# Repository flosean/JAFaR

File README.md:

# Fork from JAFaR (Just Another Fatshark Receiver Module)

__DIY OpenSource 48ch receiver OSD integrated__

The aim of the project is to build an opensource 48ch receiver for Fatshark goggles which has to be easy to develop,
upgrade and maintain. And, of course, it must be cheap!

* 48ch (8 channels for 6 bands, including race band and low race band)
* No external switch, or hall effect sensor, or buzzer, it must use __only__ the goggles buttons (up-down)
* Auto search feature
* It should include the “scanner” feature (see recent project here https://github.com/MikyM0use/OLED-scanner)
* Frequency selection via OSD inside the goggles
* I tested it only with Fatshark HD but the module should work with every Fatshark with the RX external module (like Dominator V1, V2, V3, HD, HD2...)

This project uses the “RX5808” receiver module, which can be hacked to be SPI-programmed by a microcontroller (more details later).
So what I needed is a micro controller with an easy and well-know software IDE… nothing better than Arduino. So I decided to use an Atmega 328p as micro controller.

To select the frequency there's a series of menus on the screen inside the goggles, the
useful TVOUT Arduino library is perfect and requires just a couple of resistors
(http://playground.arduino.cc/Main/TVout).
A digital switch (TS5A3359) allow to switch from OSD to the normal receiving video from the quadcopter.

The project is mainly divided into two PCBs:
* one main base module
* one "diversity" daughterboard (optional)

it's also possible to use an SPI-OLED display and use the module as standalone RX.

##Table of contents
* [Main module](#main-module)
	* [DIY Instructions](#diy-instructions)
	* [MAIN MODULE Troubleshooting](#main-module-troubleshooting)
* [Diversity module](#diversity-module)
* [OLED module](#oled-module)
* [STANDALONE mode](#standalone-mode)
* [Reference thread](#reference-thread)
* [FAQ:](#faq)
* [Donations:](#donations)

##Main module

This is the main RX module, usable alone as a receiver module, but if you connect an
"external" module, the onboard microcontroller can decide which RX module has better
reception (so-called "diversity") based on the received signal strength. Indeed, this
RX5808 modules has an analog output called RSSI proportional on the "quality" of the
received video signal. The receiving video channel (frequency) is set by the user using an OSD menu.

__MAIN MODULE (V4.1) BOM__

https://docs.google.com/spreadsheets/d/1CrZzOQHyK_d1VfHCQKwdNuoyMji0IYryI1VuffojdGA/edit?usp=sharing

__LEGACY MAIN MODULE (V3.2)__

This module is actually the same as the v4, but it doesn't have the buffer on the RSSI output,
and the PCB allows the use of a capacitor OR a resistor on the video out. DON'T use both! after some
tests I realized that a 10ohm resistor (and no cap) is enough.

(the back side is the same of the v4.0).

__LEGACY MAIN MODULE (V3.2) BOM__

https://docs.google.com/spreadsheets/d/1-763imBV3QsQ71GKDZH-BirTz1k32szNuJZUKQrE00g/edit?usp=sharing

###DIY Instructions

1. Remove the shield of the RX5808 module and desolder the resistor marked by the arrow. This
is the SPI-mod required to control the module with an external microcontroller.

2. Follow the instructions on the page https://www.arduino.cc/en/Tutorial/ArduinoISP to burn the bootloader (select __"Arduino Pro Mini 5v 16MHz"__ as target board)
using the pins in the upper right corner of the board

3. Use the FTDI connections in the left side of the board to upload the code present in the
Github page of the project. Please remember to copy all the subfolders of "libs" dir in the
libraries folder of Arduino (e.g. /Arduino/libraries).
Here you can find more infos and alternative methods to import the libraries:
https://www.arduino.cc/en/Guide/Libraries

4. When you power on the module, BOTH the leds (upper left corner of the pcb) must be on, and you must see a relatively stable splash screen for about 5 seconds

5. The very first time you power on the module, it need to calibrate itself. So please turn on the module with a working Vtx a couple of meter away (the video frequency doesn't matter). This process can take a while (about 30-50 seconds).

6. You can now use the "selection" buttons on the goggles to scroll up/down the menu to select the band

7. After the timeout of the countdown (upper left corner of the screen) you entered the frequency selection (of the selected band)

8. Scroll up/down to select the frequency and wait the timeout

9. At this moment only one led on the module has to be ON, it means that the RX video output is routed to the video_input of the goggles. If you have a Vtx near, you should see the video coming from it.

10. If you press the "selection" buttons of the goggles now, you change the frequency by the 8 frequencies of the previously selected band.

###MAIN MODULE Troubleshooting

After the initial calibration, the module must turn on in couple of seconds and you must see the splash screen for some seconds before the "band selection" screen.
In the "band selection" screen you can see the 5 bands with the percentage of the maximum RSSI detected on that band. At least one of the band must be at 98-100%.
If you "enter" one band, every channel must shows a different percentage of RSSI, otherwise the SPI-mod of the module could be failed.

__Unable to flash/Aduino issues:__

(thanks to pHysiX for the help in this section!)
Got the error "no reply" when trying to load the firmware:
the ATmega microcontroller is not soldered properly / there is a short on some pins.
try a quick solder, clean and reflow.

Got the error "incorrect signature" when trying to load the firmware:
This means Arduino is able to pick up the ATMega, but it was not communicating as expected.
This is related to poor soldering of the crystal. It's possible to do the crystal using
an iron, but I strongly recommend using flow method/hot air to do this, to make sure you
don't short the three legs accidentally onto the metal case.

__Display issues:__

They are mostly related to poor soldering for the OSD components on the board. Go back and
reflow especially the Switch, and then just make sure to clean up and touch up all the caps
and resistors near and around the switch.

If you have an external monitor, you can bypass the digital switch by power on the module with external 5v and connecting the "video in" of the monitor on the test point marked in yellow the picture:

and you should see the splash screen and the menu.

If you connect the "video in" of the monitor to the test point marked in green, you should see the initial scanning (used to determine the % of the RSSI on each channel), this means a sequence of different "fogs" and (at least) one "good" image (for a fraction of second), if you have a Vtx + cam transmitting.

__Frequency issues:__

If the module is having trouble Setting Frequency, or you are not getting video when you are
on the right channel and frequency, make sure the SPI mod has been done, and that the RX5808
is soldered on well. Pretty hard to mess this part up.

##Diversity module

The diversity module is an optional second receiver, connected to the "main" base module, it has:
* integrated linear 5v regulator with ENABLE feature connected to the VCC of the main module.
In fact power a second module from the internal goggles voltage regulator IS VERY DANGEROUS!
* an optional operational buffer for RSSI signal (I noticed that lately modules seems to be more delicate)

Please notice that because of the linear regulator on the module, it's not possible to use a 3s battery to power the diversity module.

You have two options to connect the diversity module to the base module:
* by pins: putting diversity module on top of the base one
* by jst connector: following the schematic in the image below. I used a 8-pin JST because it's used also on some FC and it's more simple to find, even if only 7 pins are used.

__DIVERSITY MODULE (V2.1) BOM__

https://docs.google.com/spreadsheets/d/1OpagubuxicmGTKqOHWwWdxZxY6wCs_DZqTYRxVoD4Tc/edit?usp=sharing

##OLED module
It's possible to use an external SPI OLED module in case of any problems with the internal OSD
or to use the module with an external monitor / different goggles.

It's important that the module has only SDA/SCL/RES/DC pins.

To use the OLED module instead of the internal OSD, uncomment  the line:

```
#define USE_OLED
```

in the file const.h

please remember to comment #define USE_DIVERSITY!

__Connections__

| ATMEGA328p pin        |  PCB silkscreen name           | OLED silkscreen name  |
| :-------------------:	|:------------------------------:| :--------------------:|
| VCC      				| 		EN 						| 		VCC 			|
| GND      				| GND 							| 					GND |
| 8      				| SSEL 							| 				SCL 	|
| A1      				| RSSI      					|   		SDA 		|
| A4 					|  NOT CONNECTED      			|    	NOT CONNECTED 	|
| 11 					| SDA      						|    DC 				|
| 13				 	| CLK      						|    RESET 				|

...or graphically:

there's also a "PCB" inside the PCBs folder, but it's just a simple adapter.

##Standalone mode

It's possible to use the project also as a standalone receiver to be used in combination
with any external monitor or other kind of goggles.

In this case you must uncomment the line

```
#define STANDALONE
```

in the file const.h. You can use the standalone mode either with OSD or with the external OLED module.

to change band/channel, the connections are the following (every normally-open momentary switch will do the job):

_UPDATE:_

it's now possible to use a "standalone module" to use the usually OSD menu on every monitor/goggles, look into /pcb/standalone_module

features:
a 5v BIG voltage regulator (up to 3/4s)
3.5mm jack output compatible with Fatshark pinout
up/down/enter joystick (work in progress to get the "back to the main menu" function by lon press the central button)
external battery /diversity module connection

__STANDALONE MODULE (V2.0) BOM__
https://docs.google.com/spreadsheets/d/1Lyl0Xg57OcXvrLwUwM6oeHDwdGa9hMxbpv7bcDlpDU4/edit?usp=sharing

##Reference thread

http://www.rcgroups.com/forums/showthread.php?t=2619124 while I'm still writing the readme :)

##FAQ

why the OSD is on the blank screen?
it’s simpler because one cannot have to recognize the vsync and the hsync pulses.

why the switch is so small and hard to solder?!?
I need a small 3-way switch, if you have a "simpler" one, just tell me :)

please note that you try and use this project AT YOUR OWN RISK!

##Donations

Hardware or paypal donations to carry on the project are always accepted.

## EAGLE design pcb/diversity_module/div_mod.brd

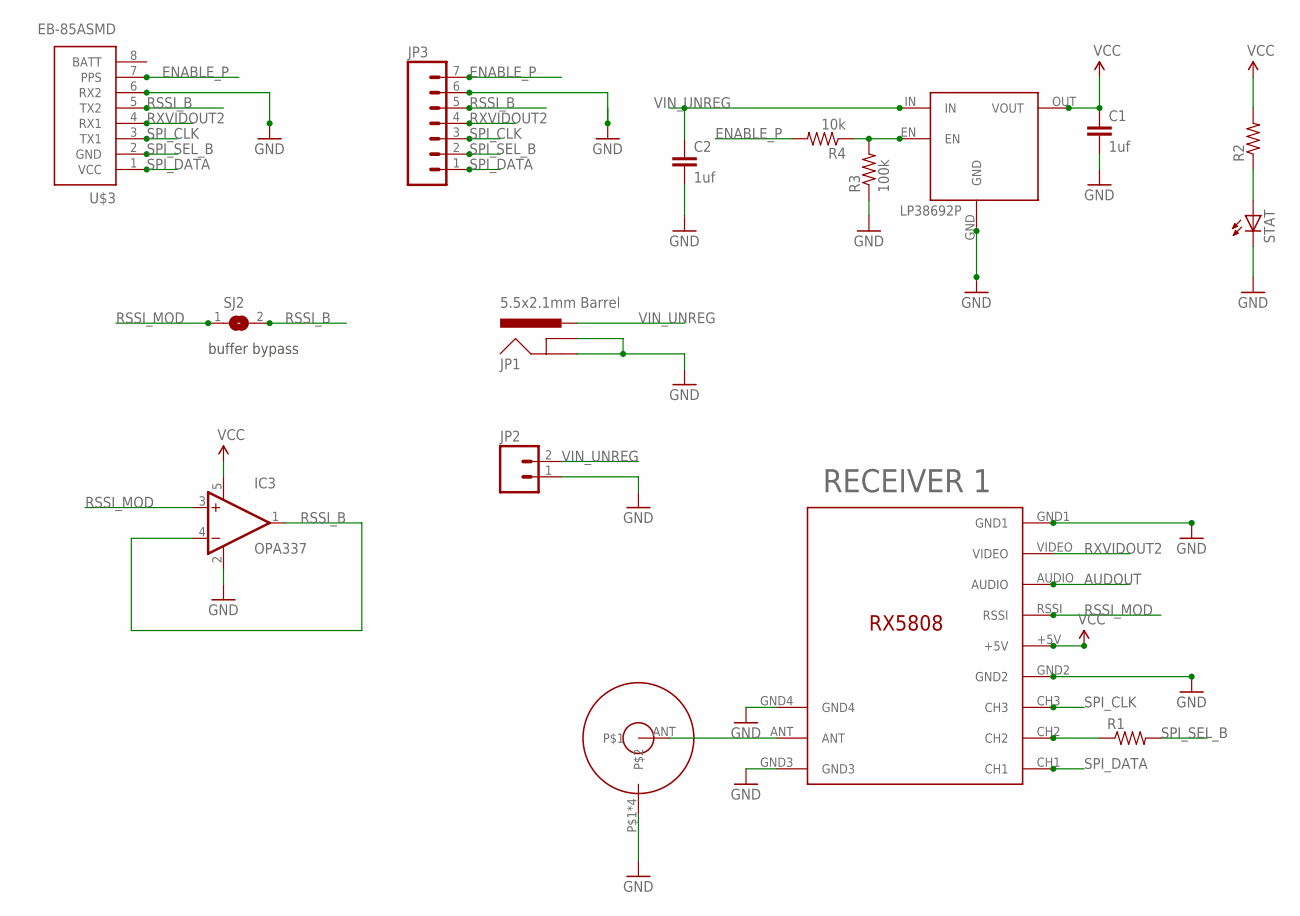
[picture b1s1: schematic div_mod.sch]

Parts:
C1, C2: 1uf; 0805
IC3: OPA336N; SOT23-5
JP1: 5.5x2.1mm Barrel; POWER_JACK_SMD
JP2: M02PTH; 1X02
JP3: M07; 1X07
R1, R2: RESISTOR0805-RES; 0805
R3: 100k; 0805
R4: 10k; 0805
RECEIVER_A: RX5808_A; RX5808
SJ2: SJ
STAT: LEDCHIP-LED0805; CHIP-LED0805
U$1: SMA_ANTENNA; SMA_CONNECTOR
U$3: EB-85ASMD; EB-85A
V1: LP38692P; TO252-51

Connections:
5V: C1.1, IC3.5 (V+), R2.2, RECEIVER_A.+5V, V1.OUT (VOUT)
AUDOUT: RECEIVER_A.AUDIO
BATT: U$3.8 (BATT)
ENABLE: R3.2, R4.1, V1.EN
ENABLE_P: JP3.7, R4.2, U$3.7 (PPS)
GND: C1.2, C2.2, IC3.2 (V-), JP1.GND (GNDBREAK), JP1.P$4 (GND), JP2.1, JP3.6, R3.1, RECEIVER_A.GND1, RECEIVER_A.GND2, RECEIVER_A.GND3, RECEIVER_A.GND4, STAT.C, U$1.P$1, U$1.P$2, U$1.P$3, U$1.P$4, U$3.6 (RX2), V1.GND
unnamed: R1.1, RECEIVER_A.CH2
unnamed: R2.1, STAT.A
unnamed: RECEIVER_A.ANT, U$1.ANT
RSSI_B: IC3.1 (OUT), IC3.4 (-IN), JP3.5, SJ2.2, U$3.5 (TX2)
RSSI_MOD: IC3.3 (+IN), RECEIVER_A.RSSI, SJ2.1
RXVIDOUT2: JP3.4, RECEIVER_A.VIDEO, U$3.4 (RX1)
SPI_CLK: JP3.3, RECEIVER_A.CH3, U$3.3 (TX1)
SPI_DATA: JP3.1, RECEIVER_A.CH1, U$3.1 (VCC)
SPI_SEL_B: JP3.2, R1.2, U$3.2 (GND)
VIN_UNREG: C2.1, JP1.VIN0 (PWR), JP2.2, V1.IN

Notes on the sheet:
RECEIVER 1
buffer bypass
OPA337

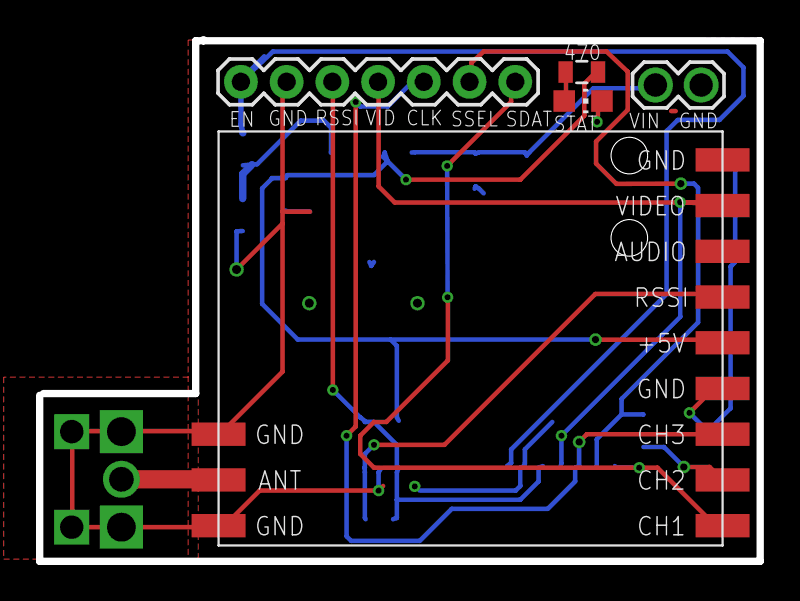
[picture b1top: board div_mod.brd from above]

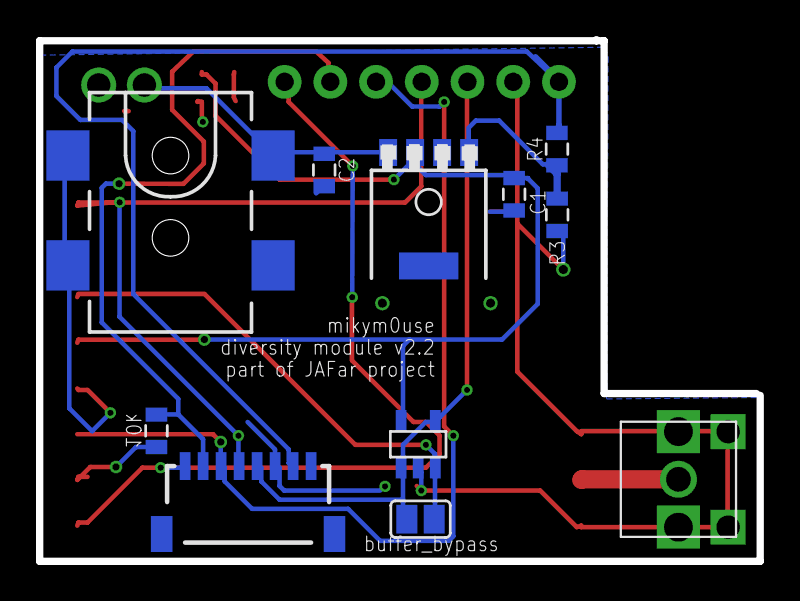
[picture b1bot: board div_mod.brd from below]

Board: 2 copper layers, 40.0 x 29.0 mm, 16 parts (11 on the bottom side), 14 nets.

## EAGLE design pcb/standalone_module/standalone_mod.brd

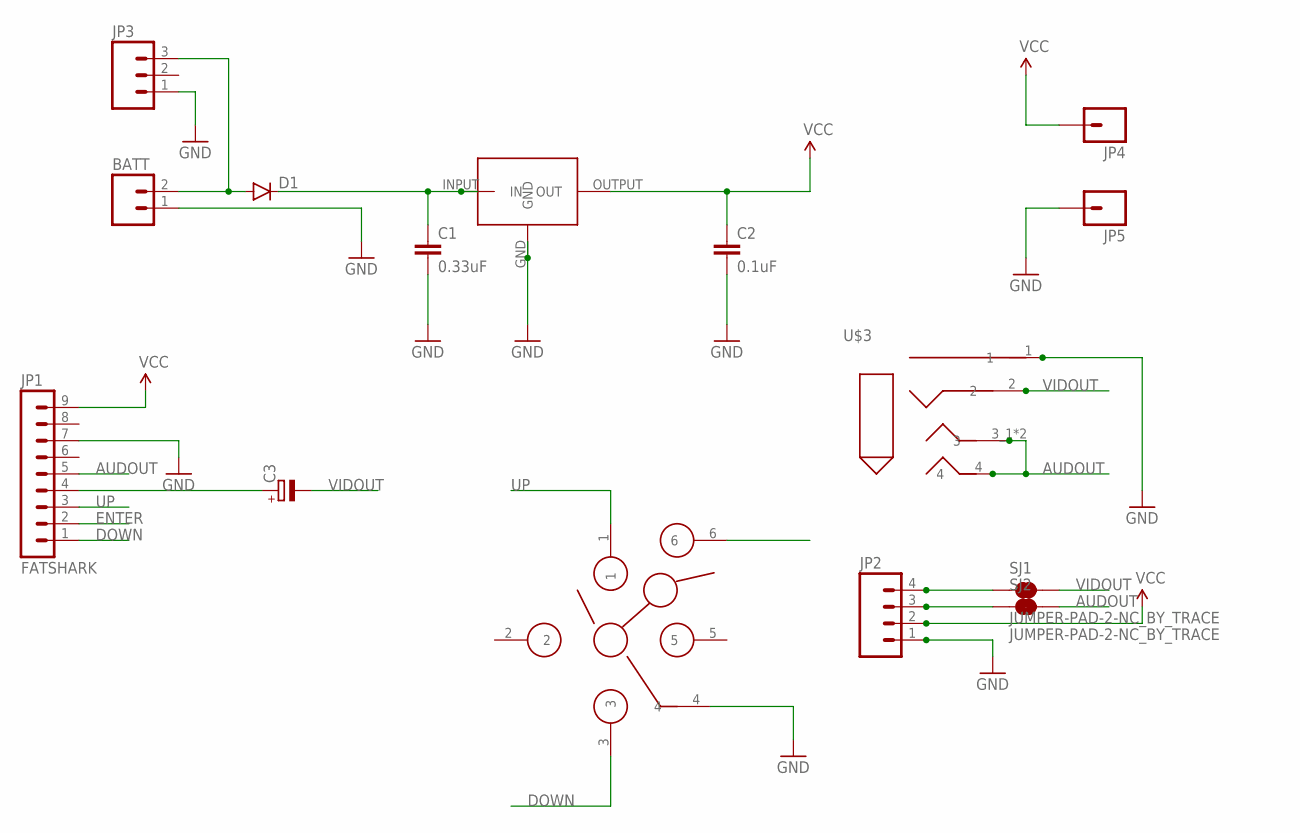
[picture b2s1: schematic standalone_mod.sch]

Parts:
BATT: M02LOCK_LONGPADS; 1X02_LOCK_LONGPADS
C1: 0.33uF; 0805
C2: 0.1uF; 0805
C3: CPOL-EUE3.5-8; E3,5-8
D1: DIODESMA; SMA-DIODE
JP1: FATSHARK; MA09-1
JP2: M04PTH; 1X04
JP3: M03LONGPADS; 1X03_LONGPADS
JP4, JP5: M01SMD; LUXEON-PAD
SJ1, SJ2: JUMPER-PAD-2-NC_BY_TRACE; PAD-JUMPER-2-NC_BY_TRACE_YES_SILK
U$1: 7805; DDPAK
U$2: SKQUCAA010
U$3: MC001293JACK; MC001293

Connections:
5V: C2.1, JP1.9, JP2.2, JP4.P$1, U$1.OUTPUT (OUT)
AUDOUT: JP1.5, SJ2.2, U$3.3_1 (3), U$3.3_2 (3), U$3.4
DOWN: JP1.1, U$2.3
ENTER: JP1.2, U$2.6
GND: BATT.1, C1.2, C2.2, JP1.7, JP2.1, JP3.1, JP5.P$1, U$1.GND, U$2.4, U$3.1
unnamed: C1.1, D1.C, U$1.INPUT (IN)
unnamed: C3.+, JP1.4
unnamed: BATT.2, D1.A, JP3.3
unnamed: JP2.4, SJ1.1
unnamed: JP2.3, SJ2.1
UP: JP1.3, U$2.1
VIDOUT: C3.-, SJ1.2, U$3.2

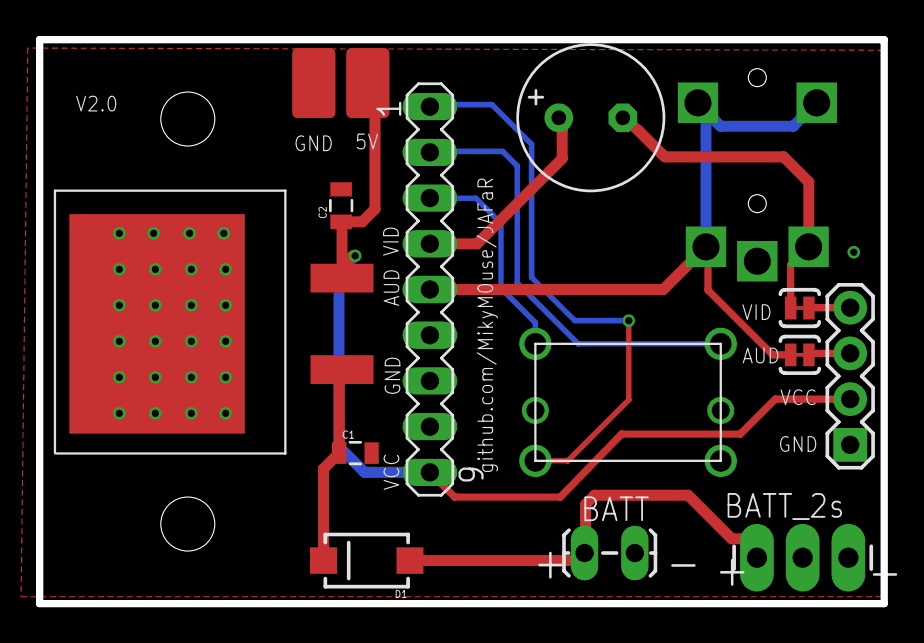
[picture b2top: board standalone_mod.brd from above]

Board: 2 copper layers, 46.9 x 31.3 mm, 15 parts (0 on the bottom side), 12 nets.

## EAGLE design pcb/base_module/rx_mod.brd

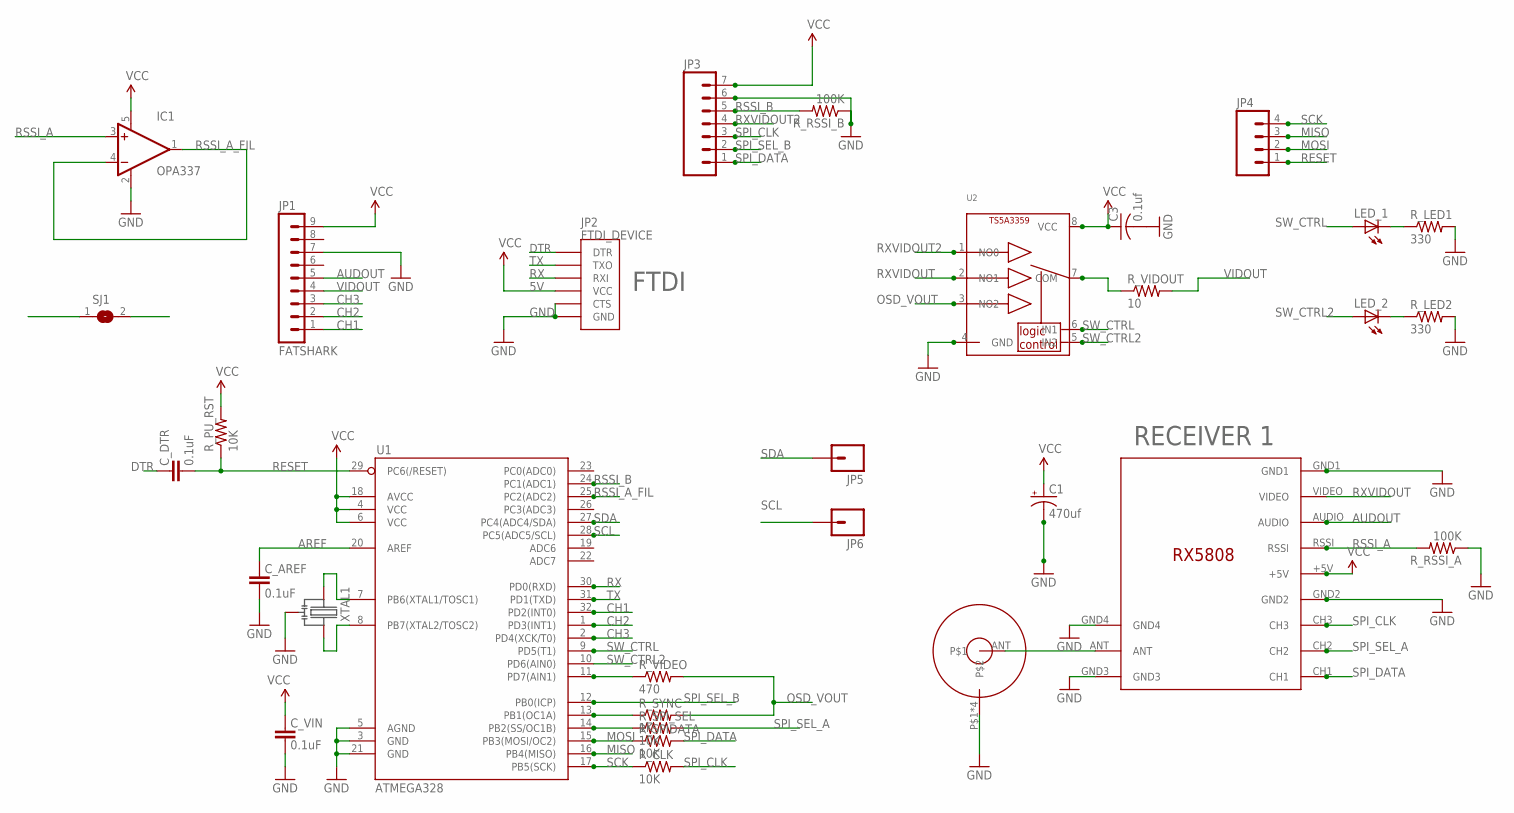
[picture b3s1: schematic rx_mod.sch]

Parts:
C1: 470uf; EIA7343
C3: 0.1uf; C0603
C_AREF: 0.1uF; 0603-CAP
C_DTR: 0.1uF; 0603-CAP
C_VIN: 0.1uF; 0603-CAP
IC1: OPA336N; SOT23-5
JP1: FATSHARK; MA09-1
JP2: FTDI_DEVICE; FTDI_DEVICE_SIDE
JP3: M07; 1X07
JP4: M04PTH; 1X04
JP5, JP6: M01SMD-4.5X1.5; PAD-1.5X4.5
LED_1, LED_2: LEDSML0603; SML0603
RECEIVER_A: RX5808_A; RX5808
R_CLK: 10K; R0805
R_LED1, R_LED2: 330; R0603
R_PU_RST: 10K; 0603-RES
R_RSSI_A: 100K; 0603-RES
R_RSSI_B: 100K; 0603-RES
R_SPIDATA: 10K; R0805
R_SPI_SEL: 10K; R0805
R_SYNC: 1K; R0805
R_VIDEO: 470; R0805
R_VIDOUT: 10; R0805
SJ1: SJ
U1: ATMEGA328; TQFP32-08
U2: TS5A3359; VFSOP-8
U$1: SMA_ANTENNA; SMA_CONNECTOR
XTAL1: CSTCE16M0V53-R0

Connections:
5V: C1.A (+), C3.1, C_VIN.2, IC1.5 (V+), JP1.9, JP2.P$4 (VCC), JP3.7, RECEIVER_A.+5V, R_PU_RST.2, U1.4 (VCC), U1.6 (VCC), U1.18 (AVCC), U2.8 (VCC)
AREF: C_AREF.2, U1.20 (AREF)
AUDOUT: JP1.5, RECEIVER_A.AUDIO
CH1: JP1.1, U1.32 (PD2(INT0))
CH2: JP1.2, U1.1 (PD3(INT1))
CH3: JP1.3, U1.2 (PD4(XCK/T0))
DTR: C_DTR.2, JP2.P$1 (DTR)
GND: C1.C (-), C3.2, C_AREF.1, C_VIN.1, IC1.2 (V-), JP1.7, JP2.P$5 (CTS), JP2.P$6 (GND), JP3.6, RECEIVER_A.GND1, RECEIVER_A.GND2, RECEIVER_A.GND3, RECEIVER_A.GND4, R_LED1.2, R_LED2.2, R_RSSI_A.1, R_RSSI_B.1, U1.3 (GND), U1.5 (AGND), U1.21 (GND), U2.4 (GND), U$1.P$1, U$1.P$2, U$1.P$3, U$1.P$4, XTAL1.2
MISO: JP4.3, U1.16 (PB4(MISO))
MOSI: JP4.2, R_SPIDATA.1, U1.15 (PB3(MOSI/OC2))
unnamed: U1.8 (PB7(XTAL2/TOSC2)), XTAL1.3
unnamed: U1.7 (PB6(XTAL1/TOSC1)), XTAL1.1
unnamed: LED_1.C, R_LED1.1
unnamed: R_SPI_SEL.1, U1.14 (PB2(SS/OC1B))
unnamed: RECEIVER_A.ANT, U$1.ANT
unnamed: R_VIDOUT.1, U2.7 (COM)
unnamed: R_SYNC.1, U1.13 (PB1(OC1A))
unnamed: R_VIDEO.1, U1.11 (PD7(AIN1))
unnamed: LED_2.C, R_LED2.1
OSD_VOUT: R_SYNC.2, R_VIDEO.2, U2.3 (NO2)
RESET: C_DTR.1, JP4.1, R_PU_RST.1, U1.29 (PC6(/RESET))
RSSI_A: IC1.3 (+IN), RECEIVER_A.RSSI, R_RSSI_A.2, SJ1.1
RSSI_A_FIL: IC1.1 (OUT), IC1.4 (-IN), SJ1.2, U1.25 (PC2(ADC2))
RSSI_B: JP3.5, R_RSSI_B.2, U1.24 (PC1(ADC1))
RX: JP2.P$3 (RXI), U1.30 (PD0(RXD))
RXVIDOUT: RECEIVER_A.VIDEO, U2.2 (NO1)
RXVIDOUT2: JP3.4, U2.1 (NO0)
SCK: JP4.4, R_CLK.1, U1.17 (PB5(SCK))
SCL: JP6.P$1, U1.28 (PC5(ADC5/SCL))
SDA: JP5.P$1, U1.27 (PC4(ADC4/SDA))
SPI_CLK: JP3.3, RECEIVER_A.CH3, R_CLK.2
SPI_DATA: JP3.1, RECEIVER_A.CH1, R_SPIDATA.2
SPI_SEL_A: RECEIVER_A.CH2, R_SPI_SEL.2
SPI_SEL_B: JP3.2, U1.12 (PB0(ICP))
SW_CTRL: LED_1.A, U1.9 (PD5(T1)), U2.6 (IN1)
SW_CTRL2: LED_2.A, U1.10 (PD6(AIN0)), U2.5 (IN2)
TX: JP2.P$2 (TXO), U1.31 (PD1(TXD))
VIDOUT: JP1.4, R_VIDOUT.2

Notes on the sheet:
RECEIVER 1
FTDI
OPA337

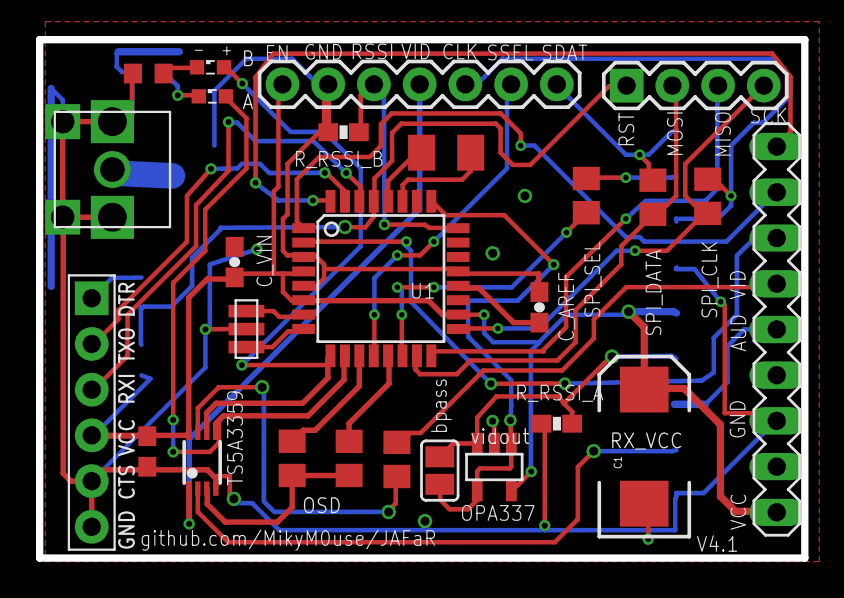
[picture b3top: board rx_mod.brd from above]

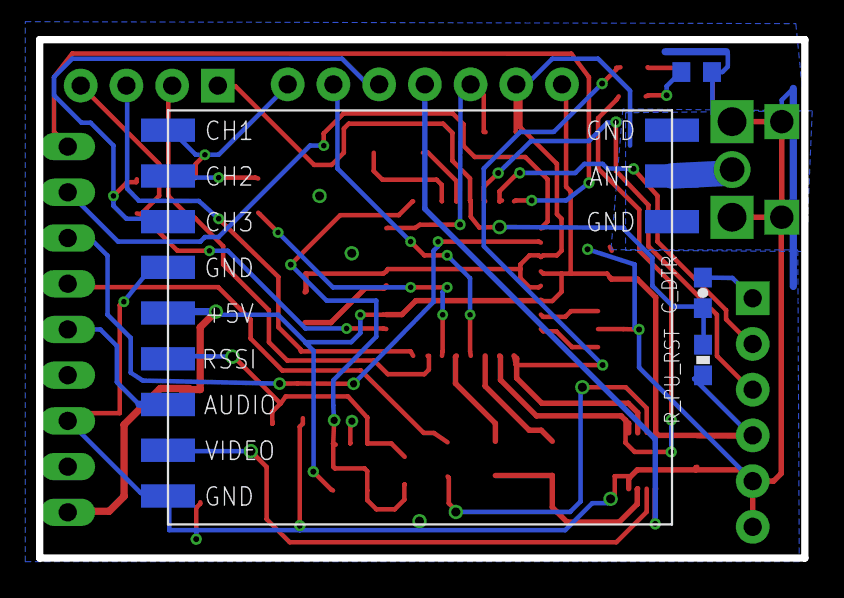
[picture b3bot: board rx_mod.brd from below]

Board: 2 copper layers, 42.5 x 28.8 mm, 31 parts (4 on the bottom side), 38 nets.

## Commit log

2016-10-18 pcb oled
2016-10-18 add raceband2
2016-10-18 switch const.h to default 48ch for testing
2016-10-24 solved issue with IDE > 1.6.9
2016-10-27 standalone module V1.0 first commit
2016-10-27 new V4.1 base module (I2C OLED pins exposed + some bug fix)
2016-10-27 add calibration of B module
2016-10-27 add dynamic menu creation - based on the goggles switch position
2016-10-28 new little menu while changing channel
2016-10-28 fix a bug with dynamic computation of diversity RSSI min value and free some ram
2016-10-29 compute_position - field tested - TODO: better filter on diversity
2016-10-30 diversity filter - first draft to test
2016-11-04 small bugs fix in case of STANDALONE
2016-11-06 add jafar delay to head
2016-11-10 standalone v2.0
2016-11-10 diversity module v2.2 - better traces and big holes for battery
2016-11-14 italian guide to flash
2016-11-14 solve broken imgs in italian flash guide
2016-11-14 standalone module v2
2016-11-22 some adjs
2016-11-24 standalone module docs
2017-01-01 div mod updates

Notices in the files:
parts and their libraries:
SparkFun-Connectors: Licensing: Creative Commons ShareAlike 4.0 International - https://creativecommons.org/licenses/by-sa/4.0
